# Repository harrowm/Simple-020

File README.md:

# Simple-020
A very simple 68020 computer .. my first attempt at a complete computer PCB ..

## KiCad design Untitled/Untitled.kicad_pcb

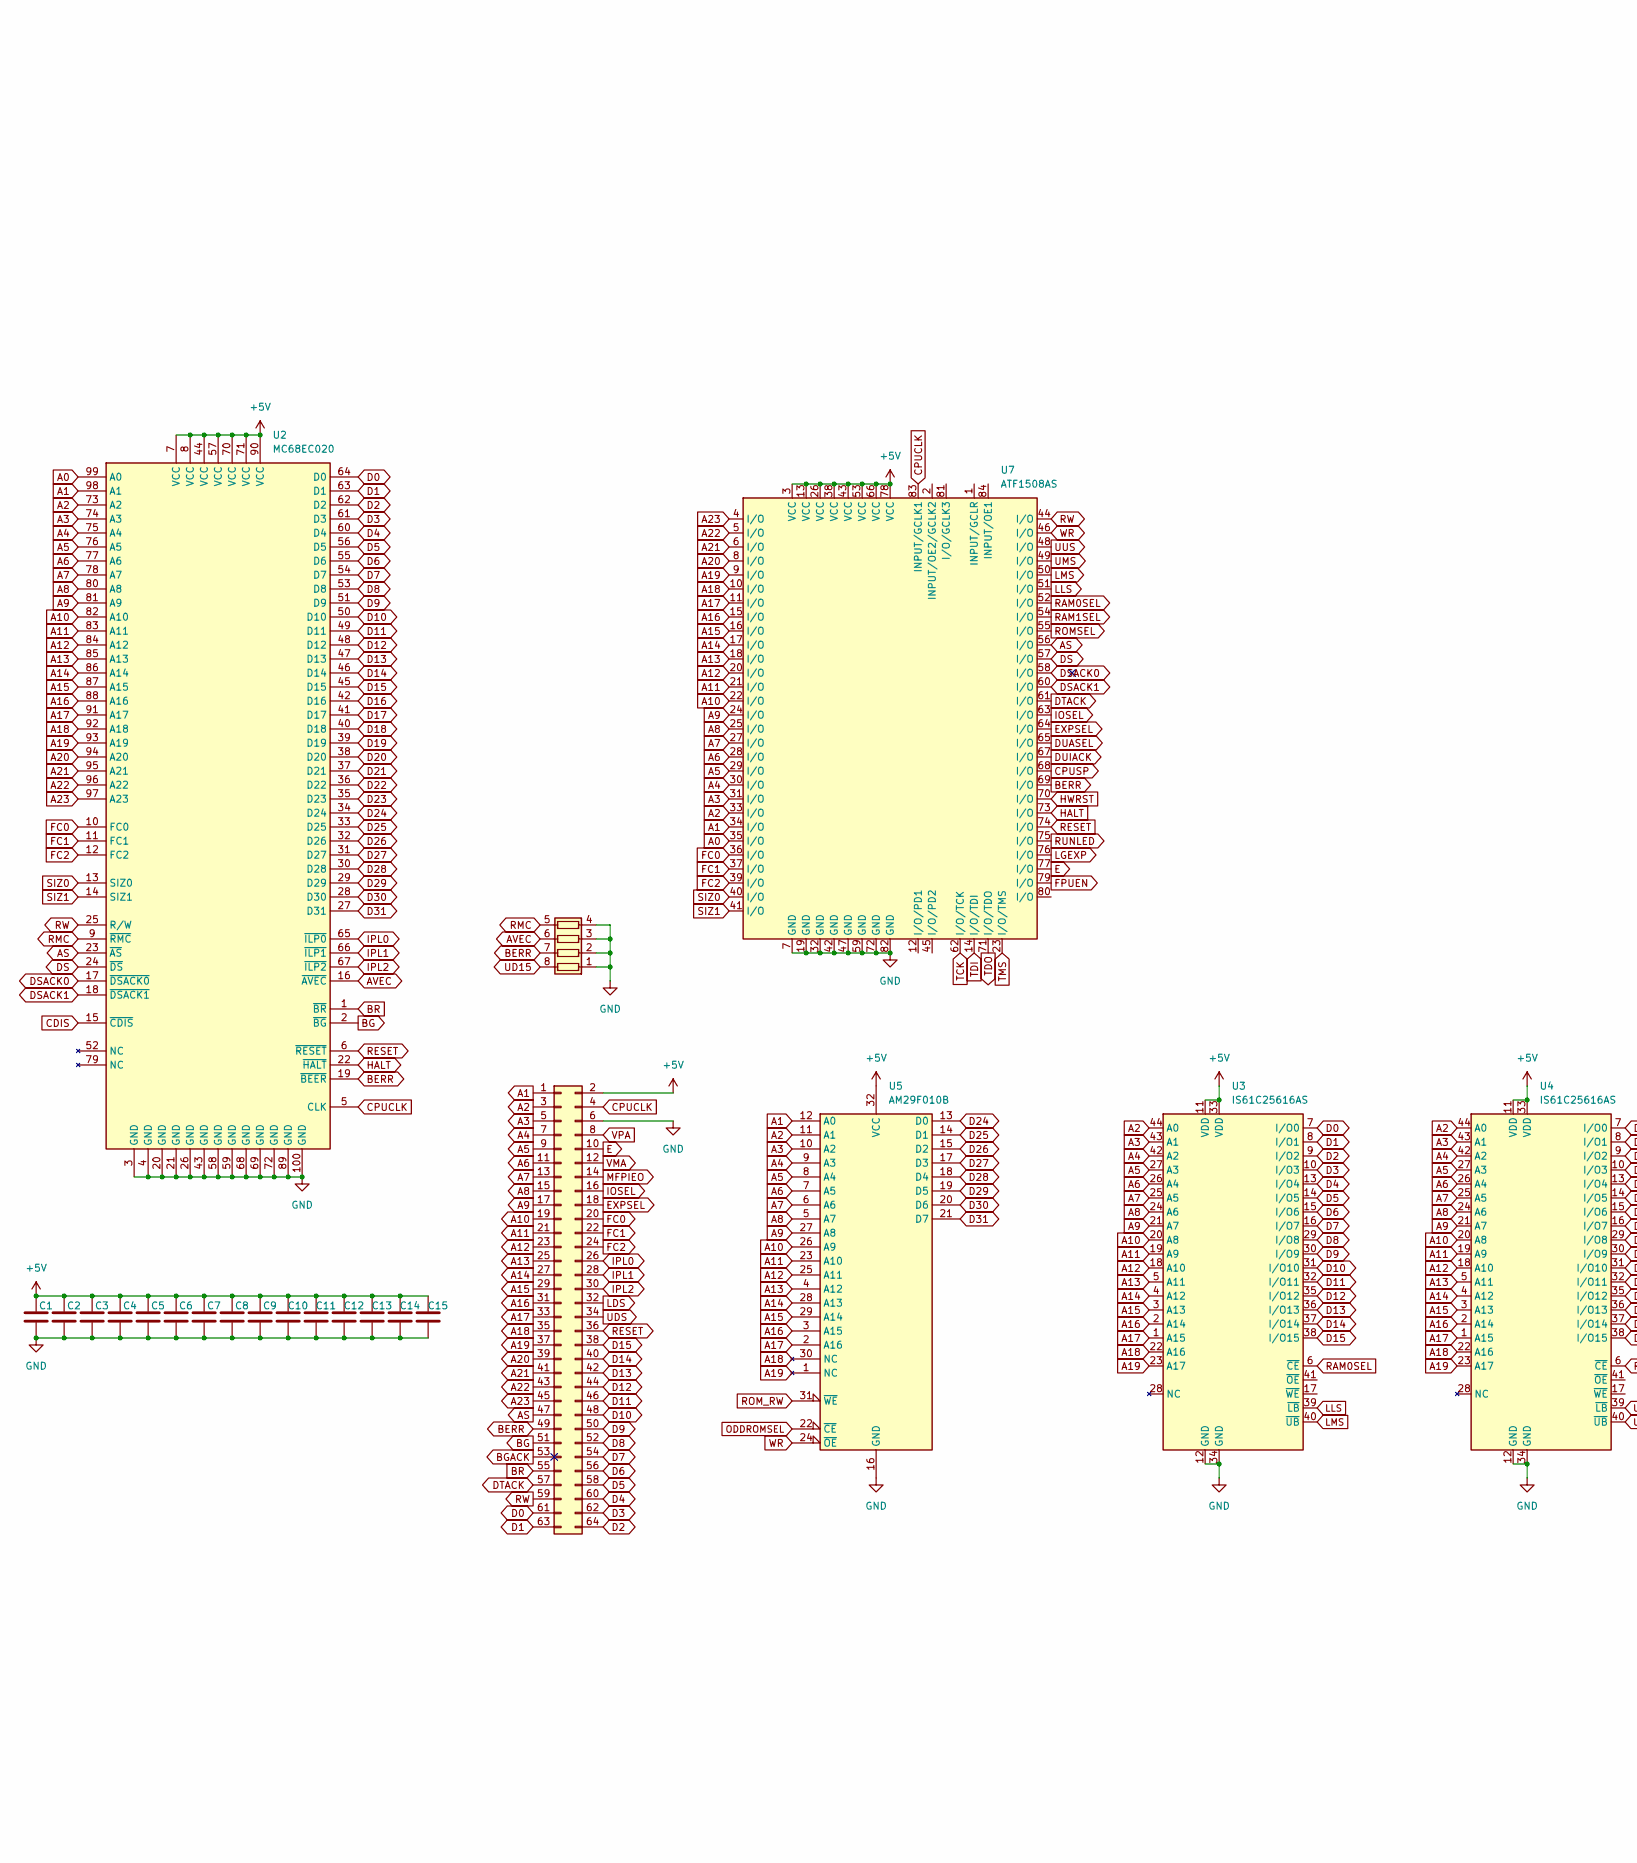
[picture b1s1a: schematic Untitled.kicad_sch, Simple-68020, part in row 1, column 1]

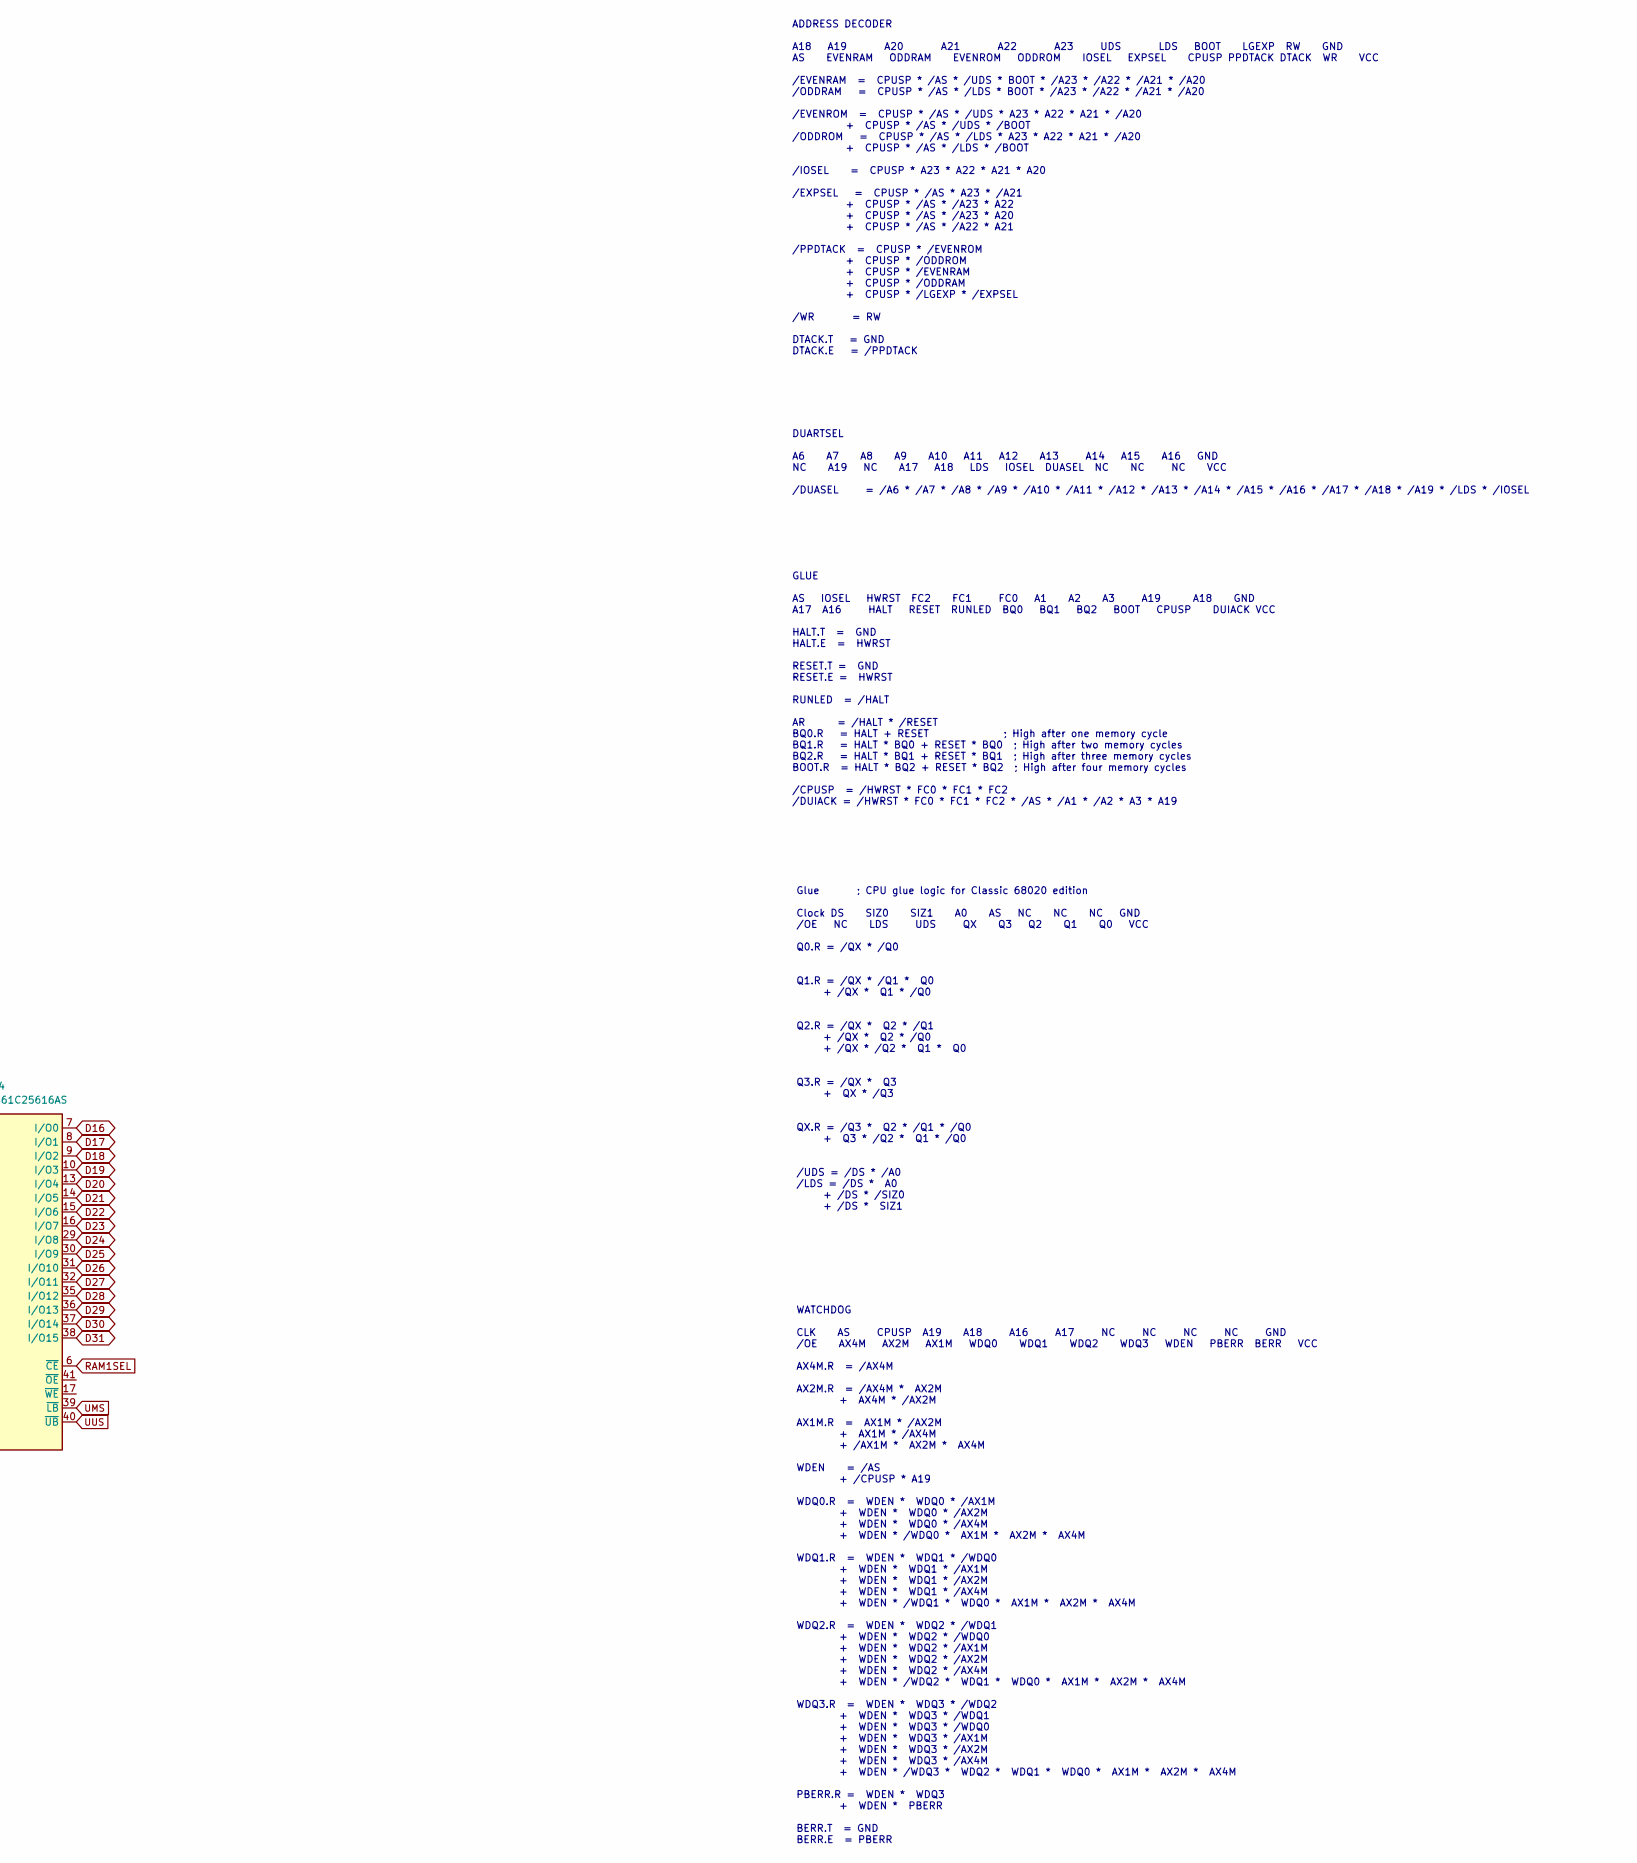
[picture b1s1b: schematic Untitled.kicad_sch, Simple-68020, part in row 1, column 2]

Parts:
BUS1: Conn_02x32_Odd_Even; PinHeader_2x32_P2.54mm_Vertical
C1, C2, C3, C4, C5, C6, C7, C8, C9, C10, C11, C12, C13, C14, C15: 100nF; C_0805_2012Metric_Pad1.18x1.45mm_HandSolder; JLC 0805
RN4: 10K; R_Array_Convex_4x0603; JLC 0603x4
U1, U6: (no value)
U2: MC68EC020; PQFP-100_14x20mm_P0.65mm
U3, U4: IS61C25616AS; TSOP-II-LongPad
U5: AM29F010B; PLCC-32_THT-Socket
U7: ATF1508AS; PLCC-84_THT-Socket

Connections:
+5V: BUS1.2, C1.1, C2.1, C3.1, C4.1, C5.1, C6.1, C7.1, C8.1, C9.1, C10.1, C11.1, C12.1, C13.1, C14.1, C15.1, U2.7 (VCC), U2.8 (VCC), U2.44 (VCC), U2.57 (VCC), U2.70 (VCC), U2.71 (VCC), U2.90 (VCC), U3.11 (VDD), U3.33 (VDD), U4.11 (VDD), U4.33 (VDD), U5.32 (VCC), U7.3 (VCC), U7.13 (VCC), U7.26 (VCC), U7.38 (VCC), U7.43 (VCC), U7.53 (VCC), U7.66 (VCC), U7.78 (VCC)
A0: U2.99 (A0), U7.35 (I/O)
A1: BUS1.1, U2.98 (A1), U5.12 (A0), U7.34 (I/O)
A2: BUS1.3, U2.73 (A2), U3.44 (A0), U4.44 (A0), U5.11 (A1), U7.33 (I/O)
A3: BUS1.5, U2.74 (A3), U3.43 (A1), U4.43 (A1), U5.10 (A2), U7.31 (I/O)
A4: BUS1.7, U2.75 (A4), U3.42 (A2), U4.42 (A2), U5.9 (A3), U7.30 (I/O)
A5: BUS1.9, U2.76 (A5), U3.27 (A3), U4.27 (A3), U5.8 (A4), U7.29 (I/O)
A6: BUS1.11, U2.77 (A6), U3.26 (A4), U4.26 (A4), U5.7 (A5), U7.28 (I/O)
A7: BUS1.13, U2.78 (A7), U3.25 (A5), U4.25 (A5), U5.6 (A6), U7.27 (I/O)
A8: BUS1.15, U2.80 (A8), U3.24 (A6), U4.24 (A6), U5.5 (A7), U7.25 (I/O)
A9: BUS1.17, U2.81 (A9), U3.21 (A7), U4.21 (A7), U5.27 (A8), U7.24 (I/O)
A10: BUS1.19, U2.82 (A10), U3.20 (A8), U4.20 (A8), U5.26 (A9), U7.22 (I/O)
A11: BUS1.21, U2.83 (A11), U3.19 (A9), U4.19 (A9), U5.23 (A10), U7.21 (I/O)
A12: BUS1.23, U2.84 (A12), U3.18 (A10), U4.18 (A10), U5.25 (A11), U7.20 (I/O)
A13: BUS1.25, U2.85 (A13), U3.5 (A11), U4.5 (A11), U5.4 (A12), U7.18 (I/O)
A14: BUS1.27, U2.86 (A14), U3.4 (A12), U4.4 (A12), U5.28 (A13), U7.17 (I/O)
A15: BUS1.29, U2.87 (A15), U3.3 (A13), U4.3 (A13), U5.29 (A14), U7.16 (I/O)
A16: BUS1.31, U2.88 (A16), U3.2 (A14), U4.2 (A14), U5.3 (A15), U7.15 (I/O)
A17: BUS1.33, U2.91 (A17), U3.1 (A15), U4.1 (A15), U5.2 (A16), U7.11 (I/O)
A18: BUS1.35, U2.92 (A18), U3.22 (A16), U4.22 (A16), U5.30 (NC), U7.10 (I/O)
A19: BUS1.37, U2.93 (A19), U3.23 (A17), U4.23 (A17), U5.1 (NC), U7.9 (I/O)
A20: BUS1.39, U2.94 (A20), U7.8 (I/O)
A21: BUS1.41, U2.95 (A21), U7.6 (I/O)
A22: BUS1.43, U2.96 (A22), U7.5 (I/O)
A23: BUS1.45, U2.97 (A23), U7.4 (I/O)
AS: BUS1.47, U2.23 (~AS), U7.56 (I/O)
AVEC: RN4.6 (R3.2), U2.16 (~AVEC)
BERR: BUS1.49, RN4.7 (R2.2), U2.19 (~BEER), U7.69 (I/O)
BG: BUS1.51, U2.2 (~BG)
BGACK: BUS1.53
BR: BUS1.55, U2.1 (~BR)
CDIS: U2.15 (~CDIS)
CPUCLK: BUS1.4, U2.5 (CLK), U7.83 (INPUT/GCLK1)
CPUSP: U7.68 (I/O)
D0: BUS1.61, U2.64 (D0), U3.7 (I/O0)
D1: BUS1.63, U2.63 (D1), U3.8 (I/O1)
D2: BUS1.64, U2.62 (D2), U3.9 (I/O2)
D3: BUS1.62, U2.61 (D3), U3.10 (I/O3)
D4: BUS1.60, U2.60 (D4), U3.13 (I/O4)
D5: BUS1.58, U2.56 (D5), U3.14 (I/O5)
D6: BUS1.56, U2.55 (D6), U3.15 (I/O6)
D7: BUS1.54, U2.54 (D7), U3.16 (I/O7)
D8: BUS1.52, U2.53 (D8), U3.29 (I/O8)
D9: BUS1.50, U2.51 (D9), U3.30 (I/O9)
D10: BUS1.48, U2.50 (D10), U3.31 (I/O10)
D11: BUS1.46, U2.49 (D11), U3.32 (I/O11)
D12: BUS1.44, U2.48 (D12), U3.35 (I/O12)
D13: BUS1.42, U2.47 (D13), U3.36 (I/O13)
D14: BUS1.40, U2.46 (D14), U3.37 (I/O14)
D15: BUS1.38, U2.45 (D15), U3.38 (I/O15)
D16: U2.42 (D16), U4.7 (I/O0)
D17: U2.41 (D17), U4.8 (I/O1)
D18: U2.40 (D18), U4.9 (I/O2)
D19: U2.39 (D19), U4.10 (I/O3)
D20: U2.38 (D20), U4.13 (I/O4)
D21: U2.37 (D21), U4.14 (I/O5)
D22: U2.36 (D22), U4.15 (I/O6)
D23: U2.35 (D23), U4.16 (I/O7)
D24: U2.34 (D24), U4.29 (I/O8), U5.13 (D0)
D25: U2.33 (D25), U4.30 (I/O9), U5.14 (D1)
D26: U2.32 (D26), U4.31 (I/O10), U5.15 (D2)
D27: U2.31 (D27), U4.32 (I/O11), U5.17 (D3)
D28: U2.30 (D28), U4.35 (I/O12), U5.18 (D4)
D29: U2.29 (D29), U4.36 (I/O13), U5.19 (D5)
D30: U2.28 (D30), U4.37 (I/O14), U5.20 (D6)
D31: U2.27 (D31), U4.38 (I/O15), U5.21 (D7)
DS: U2.24 (~DS), U7.57 (I/O)
DSACK0: U2.17 (~DSACK0), U7.58 (I/O)
DSACK1: U2.18 (~DSACK1), U7.60 (I/O)
DTACK: BUS1.57, U7.61 (I/O)
DUASEL: U7.65 (I/O)
DUIACK: U7.67 (I/O)
E: BUS1.10, U7.77 (I/O)
EXPSEL: BUS1.18, U7.64 (I/O)
FC0: BUS1.20, U2.10 (FC0), U7.36 (I/O)
FC1: BUS1.22, U2.11 (FC1), U7.37 (I/O)
FC2: BUS1.24, U2.12 (FC2), U7.39 (I/O)
FPUEN: U7.79 (I/O)
GND: BUS1.6, C1.2, C2.2, C3.2, C4.2, C5.2, C6.2, C7.2, C8.2, C9.2, C10.2, C11.2, C12.2, C13.2, C14.2, C15.2, RN4.1 (R1.1), RN4.2 (R2.1), RN4.3 (R3.1), RN4.4 (R4.1), U2.3 (GND), U2.4 (GND), U2.20 (GND), U2.21 (GND), U2.26 (GND), U2.43 (GND), U2.58 (GND), U2.59 (GND), U2.68 (GND), U2.69 (GND), U2.72 (GND), U2.89 (GND), U2.100 (GND), U3.12 (GND), U3.34 (GND), U4.12 (GND), U4.34 (GND), U5.16 (GND), U7.7 (GND), U7.19 (GND), U7.32 (GND), U7.42 (GND), U7.47 (GND), U7.59 (GND), U7.72 (GND), U7.82 (GND); also elsewhere on the board
HALT: U2.22 (~HALT), U7.73 (I/O)
HWRST: U7.70 (I/O)
IOSEL: BUS1.16, U7.63 (I/O)
IPL0: BUS1.26, U2.65 (~ILP0)
IPL1: BUS1.28, U2.66 (~ILP1)
IPL2: BUS1.30, U2.67 (~ILP2)
LDS: BUS1.32
LGEXP: U7.76 (I/O)
LLS: U3.39 (~LB), U7.51 (I/O)
LMS: U3.40 (~UB), U7.50 (I/O)
MFPIEO: BUS1.14
ODDROMSEL: U5.22 (~CE)
RAM0SEL: U3.6 (~CE), U7.52 (I/O)
RAM1SEL: U4.6 (~CE), U7.54 (I/O)
RESET: BUS1.36, U2.6 (~RESET), U7.74 (I/O)
RMC: RN4.5 (R4.2), U2.9 (~RMC)
ROMSEL: U7.55 (I/O)
ROM_RW: U5.31 (~WE)
RUNLED: U7.75 (I/O)
RW: BUS1.59, U2.25 (R/W), U7.44 (I/O)
SIZ0: U2.13 (SIZ0), U7.40 (I/O)
SIZ1: U2.14 (SIZ1), U7.41 (I/O)
TCK: U7.62 (I/O/TCK)
TDI: U7.14 (I/O/TDI)
TDO: U7.71 (I/O/TDO)
TMS: U7.23 (I/O/TMS)
UD15: RN4.8 (R1.2)
UDS: BUS1.34
UMS: U4.39 (~LB), U7.49 (I/O)
UUS: U4.40 (~UB), U7.48 (I/O)
VMA: BUS1.12
VPA: BUS1.8
WR: U5.24 (~OE), U7.46 (I/O)

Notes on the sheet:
ADDRESS DECODER A18 A19 A20 A21 A22 A23 UDS LDS BOOT LGEXP RW GND AS EVENRAM ODDRAM EVENROM ODDROM IOSEL EXPSEL CPUSP PPDTACK DTACK WR VCC /EVENRAM = CPUSP * /AS * /UDS * BOOT * /A23 * /A22 * /A21 * /A20 /ODDRAM = CPUSP * /AS * /LDS * BOOT * /A23 * /A22 * /A21 * /A20 /EVENROM = CPUSP * /AS * /UDS *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
WATCHDOG CLK AS CPUSP A19 A18 A16 A17 NC NC NC NC GND /OE AX4M AX2M AX1M WDQ0 WDQ1 WDQ2 WDQ3 WDEN PBERR BERR VCC AX4M.R = /AX4M AX2M.R = /AX4M * AX2M + AX4M * /AX2M AX1M.R = AX1M * /AX2M + AX1M * /AX4M + /AX1M * AX2M * AX4M WDEN = /AS + /CPUSP * A19 WDQ0.R = WDEN * WDQ0 * /AX1M + WDEN * WDQ0 * /AX2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
DUARTSEL A6 A7 A8 A9 A10 A11 A12 A13 A14 A15 A16 GND NC A19 NC A17 A18 LDS IOSEL DUASEL NC NC NC VCC /DUASEL = /A6 * /A7 * /A8 * /A9 * /A10 * /A11 * /A12 * /A13 * /A14 * /A15 * /A16 * /A17 * /A18 * /A19 * /LDS * /IOSEL
Glue ; CPU glue logic for Classic 68020 edition Clock DS SIZ0 SIZ1 A0 AS NC NC NC GND /OE NC LDS UDS QX Q3 Q2 Q1 Q0 VCC Q0.R = /QX * /Q0 Q1.R = /QX * /Q1 * Q0 + /QX * Q1 * /Q0 Q2.R = /QX * Q2 * /Q1 + /QX * Q2 * /Q0 + /QX * /Q2 * Q1 * Q0 Q3.R = /QX * Q3 + QX * /Q3 QX.R = /Q3 * Q2 * /Q1 * /Q0 + Q3 * 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
GLUE AS IOSEL HWRST FC2 FC1 FC0 A1 A2 A3 A19 A18 GND A17 A16 HALT RESET RUNLED BQ0 BQ1 BQ2 BOOT CPUSP DUIACK VCC HALT.T = GND HALT.E = HWRST RESET.T = GND RESET.E = HWRST RUNLED = /HALT AR = /HALT * /RESET BQ0.R = HALT + RESET ; High after one memory cycle BQ1.R = HALT * BQ0 + RESET * BQ0 ; High af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

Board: 4 copper layers, 25 parts (0 on the bottom side), 90 nets, no tracks yet.

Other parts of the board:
RN1, RN2, RN3: 10K; R_Array_Convex_4x0603

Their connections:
GND: RN1.1 (R1.1), RN1.2 (R2.1), RN1.3 (R3.1), RN1.4 (R4.1), RN2.1 (R1.1), RN2.2 (R2.1), RN2.3 (R3.1), RN2.4 (R4.1), RN3.1 (R1.1), RN3.2 (R2.1), RN3.3 (R3.1), RN3.4 (R4.1); also elsewhere on the board

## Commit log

2024-04-05 Upgrade to ATF1508

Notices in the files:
Untitled/Untitled.kicad_sch:
Malcolm Harrow, 2024, MIT License
